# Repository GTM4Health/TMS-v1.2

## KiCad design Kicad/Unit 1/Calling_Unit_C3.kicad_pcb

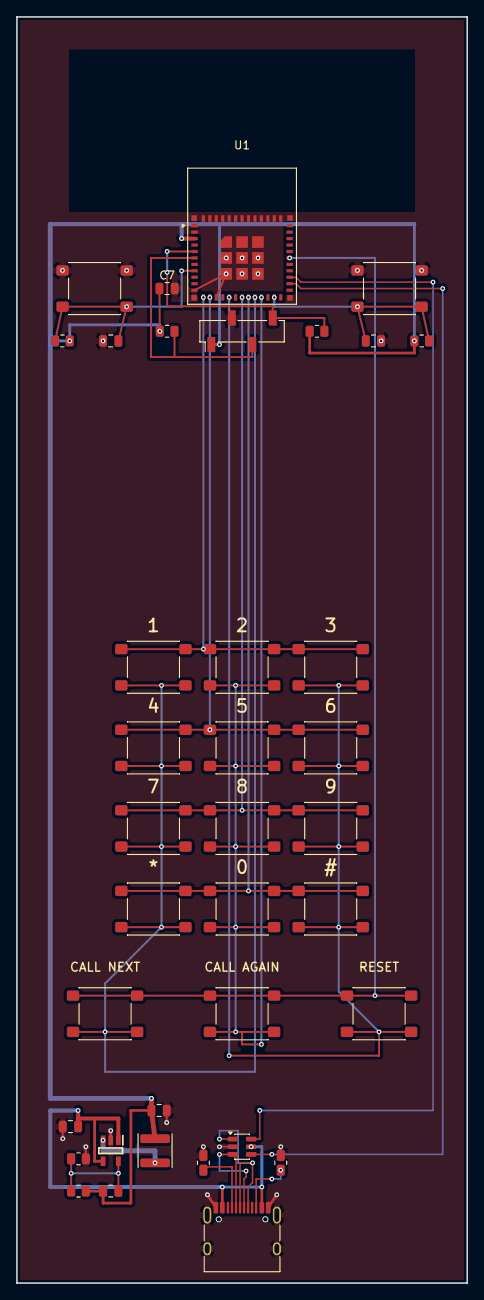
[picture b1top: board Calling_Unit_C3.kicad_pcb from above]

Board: 2 copper layers, 55.9 x 157.1 mm, 37 parts (0 on the bottom side), 23 nets.

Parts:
C1: 10uF; C1
C2: 22uF; C2
C4: C_0805_2012Metric; C4
C5: C_0805_2012Metric; C5
C6: 22pF; C_0805_2012Metric
C7: 100nF; C_0805_2012Metric
D1: SOT-23-6; D1
J1: USB_C_Receptacle_HRO_TYPE-C-31-M-12; USB_C_Receptacle_GCT_USB4105-xx-A_16P_TopMnt_Horizontal
L1: 1.0uH; L_Sunlord_SWPA4020S
R1: R_0805_2012Metric; R1
R2: R_0805_2012Metric; R2
R3: R_0805_2012Metric; R3
R7: R_0805_2012Metric; R7
R11: 100k; R_0805_2012Metric
R12: 22.1k; R_0805_2012Metric
R15, R16: 4.7k; R_0805_2012Metric
SW4: SW_SPST_PTS645Sx43SMTR92; SW4
SW5: SW_SPST_PTS645Sx43SMTR92; SW5
SW6: SW_SPST_PTS645Sx43SMTR92; SW6
SW7: SW_SPST_PTS645Sx43SMTR92; SW7
SW8: SW_SPST_PTS645Sx43SMTR92; SW8
SW9: SW_SPST_PTS645Sx43SMTR92; SW9
SW10: SW_SPST_PTS645Sx43SMTR92; SW10
SW11: SW_SPST_PTS645Sx43SMTR92; SW11
SW12: SW_SPST_PTS645Sx43SMTR92; SW12
SW13: SW_SPST_PTS645Sx43SMTR92; SW13
SW14: SW_SPST_PTS645Sx43SMTR92; SW14
SW15: SW_SPST_PTS645Sx43SMTR92; SW15
SW16: SW_SPST_PTS645Sx43SMTR92; SW16
SW17: SW_SPST_PTS645Sx43SMTR92; SW17
SW18: SW_SPST_PTS645Sx43SMTR92; SW18
SW19: SW_SPST_PTS645Sx43SMTR92; SW19
SW20: SW_SPST_PTS645Sx43SMTR92; SW20
U1: ESP32-C3-MINI-1; ESP32C3MINI1N4X
U2: SY8089A1AAC; SOT95P285X130-5N
U4: SH1106_1.3_OLED; PinSocket_1x04_P2.54mm_Vertical_SMD_Pin1Left

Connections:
/COL1: SW6.2, SW9.2, SW10.2, SW14.2, SW18.2, U1.20
/COL2: SW7.2, SW11.2, SW13.2, SW15.2, SW19.2, U1.21
/COL3: SW8.2, SW12.2, SW16.2, SW17.2, SW20.2, U1.16
/ESP: C2.1, C6.1, C7.1, L1.2, R3.1, R7.1, R11.1, R15.1, R16.1, U1.3, U4.1
/ROW1: SW6.1, SW7.1, SW8.1, U1.12
/ROW2: SW10.1, SW11.1, SW12.1, U1.13
/ROW3: SW14.1, SW15.1, SW16.1, U1.18
/ROW4: SW18.1, SW19.1, SW20.1, U1.19
/ROW5: SW9.1, SW13.1, SW17.1, U1.30
/SCL: R16.2, U1.6, U4.3
/SDA: R15.2, U1.5, U4.4
/USB C: C1.1, D1.5, J1.A4, J1.A9, J1.B4, J1.B9, U2.1, U2.4
/USB_D+: D1.6, U1.27
/USB_D-: D1.4, U1.26
GND: C1.2, C2.2, C4.2, C5.2, C7.2, D1.2, J1.A1, J1.A12, J1.B1, J1.B12, J1.SH, R1.2, R2.2, R12.2, SW4.1, SW5.1, U1.1, U1.2, U1.11, U1.14, U1.36, U1.37, U1.38, U1.39, U1.40, U1.41, U1.42, U1.43, U1.44, U1.45, U1.46, U1.47, U1.48, U1.49, U1.50, U1.51, U1.52, U1.53, U2.2, U4.2
unnamed: D1.1, J1.A6, J1.B6
unnamed: D1.3, J1.A7, J1.B7
unnamed: J1.A5, R1.1
unnamed: J1.B5, R2.1
unnamed: C4.1, R3.2, SW4.2, U1.8
unnamed: C5.1, R7.2, SW5.2, U1.23
unnamed: C6.2, R11.2, R12.1, U2.5
unnamed: L1.1, U2.3

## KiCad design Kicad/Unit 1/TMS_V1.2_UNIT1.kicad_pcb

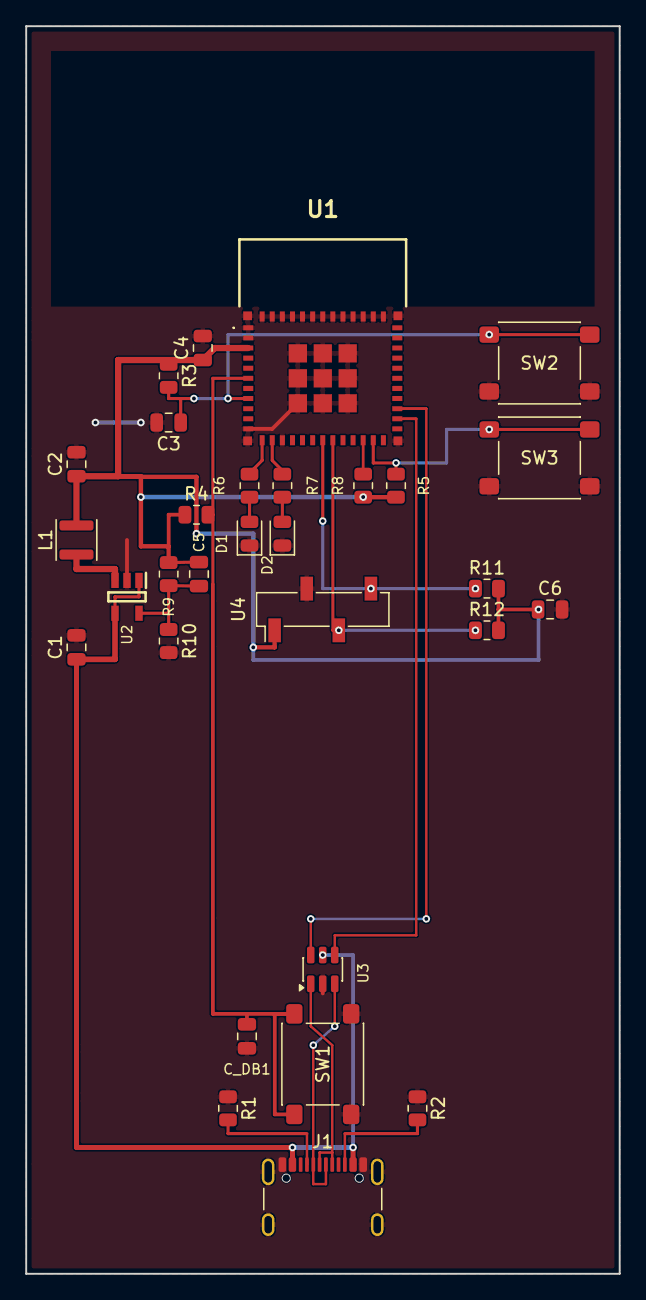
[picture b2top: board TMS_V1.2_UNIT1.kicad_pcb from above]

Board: 2 copper layers, 47.0 x 98.8 mm, 30 parts (0 on the bottom side), 21 nets.

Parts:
C1: 10uF; C_0805_2012Metric
C2: 22uF; C_0805_2012Metric
C3: 1uF; C_0805_2012Metric
C4, C6: 100nF; C_0805_2012Metric
C5: 22pF; C_0805_2012Metric
C_DB1: 100nF; C_0805_2012Metric
D1, D2: LED; LED_0805_2012Metric
J1: USB4105-GF-A; USB_C_Receptacle_GCT_USB4105-xx-A_16P_TopMnt_Horizontal
L1: 2.2uH; L_Sunlord_SWPA3015S
R1, R2: 5.1k; R_0805_2012Metric
R3, R4, R5, R8: 10k; R_0805_2012Metric
R6, R7: 470; R_0805_2012Metric
R9: 100k; R_0805_2012Metric
R10: 22.1k; R_0805_2012Metric
R11, R12: 4.7k; R_0805_2012Metric
SW1: TOKEN_BTN; SW_SPST_PTS645Sx43SMTR92
SW2: EN; SW_SPST_PTS645Sx43SMTR92
SW3: Boot; SW_SPST_PTS645Sx43SMTR92
U1: ESP32-C3-MINI-1-N4X; ESP32C3MINI1N4X
U2: SY8089A1AAC; SOT95P285X130-5N
U3: USBLC6-2SC6; SOT-23-6
U4: OLED_1.2_I2C; PinSocket_1x04_P2.54mm_Vertical_SMD_Pin1Left

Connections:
/3V3: C2.1, C4.1, C5.1, C6.1, L1.2, R3.1, R4.1, R5.1, R8.1, R9.1, R11.2, R12.2, U1.3 (3V3), U4.1
/BOOT_BUTTON: R5.2, SW3.1, U1.23 (IO9)
/I2C_SCL: R12.1, U1.19 (IO5), U4.3
/I2C_SDA: R11.1, U1.18 (IO4), U4.4
/POWER_LED: R6.1, U1.12 (IO0)
/RESET: C3.1, R3.2, SW2.1, U1.8 (EN)
/Step Down: C1.1, J1.A4 (VBUS), J1.A9 (VBUS), J1.B4 (VBUS), J1.B9 (VBUS), U2.1, U2.4, U3.5 (VBUS)
/TOKEN_GENERATION_BTN: C_DB1.1, R4.2, SW1.1, U1.6 (IO3)
/USB_D+: U1.27 (IO19), U3.6 (I/O1)
/USB_D-: U1.26 (IO18), U3.4 (I/O2)
/WIFI_LED: R7.1, U1.13 (IO1)
GND: C1.2, C2.2, C3.2, C4.2, C6.2, C_DB1.2, D1.1 (K), D2.1 (K), J1.A1 (GND), J1.A12 (GND), J1.B1 (GND), J1.B12 (GND), J1.SH (SHIELD), R1.1, R2.1, R10.2, SW1.2, SW2.2, SW3.2, U1.1 (GND_1), U1.2 (GND_2), U1.11 (GND_3), U1.14 (GND_4), U1.36 (GND_5), U1.37 (GND_6), U1.38 (GND_7), U1.39 (GND_8), U1.40 (GND_9), U1.41 (GND_10), U1.42 (GND_11), U1.43 (GND_12), U1.44 (GND_13), U1.45 (GND_14), U1.46 (GND_15), U1.47 (GND_16), U1.48 (GND_17), U1.49 (GND_18), U1.50 (GND_19), U1.51 (GND_20), U1.52 (GND_21), U1.53 (GND_22), U1.54 (GND_23), U1.55 (GND_24), U1.56 (GND_25), U1.57 (GND_26), U1.58 (GND_27), U1.59 (GND_28), U1.60 (GND_29), U1.61 (GND_30), U2.2, U3.2 (GND), U4.2
unnamed: D1.2 (A), R6.2
unnamed: D2.2 (A), R7.2
unnamed: J1.A5 (CC1), R1.2
unnamed: J1.B5 (CC2), R2.2
unnamed: J1.A6 (D+), J1.B6 (D+), U3.1 (I/O1)
unnamed: J1.A7 (D-), J1.B7 (D-), U3.3 (I/O2)
unnamed: R8.2, U1.22 (IO8)
unnamed: C5.2, R9.2, R10.1, U2.5
unnamed: L1.1, U2.3
